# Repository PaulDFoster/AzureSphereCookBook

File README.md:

# AzureSphereCookBook
A collection of Azure Sphere code projects

1. Programmatic Reset: Programmatically trigger a Azure Sphere RDB reset using GPIO
2. Azure Blob Storage blob download using libcurl
3. Simple SPI communication. This project was built to demonstrate SPI comms to an ESP8266
4. SPI Flash Memory. Simple utilisation of an SPI flash memory to extend storage
5. Cifar10 CMSIS-NN example for Azure Sphere Cortex-M4F core
6. Eagle library for AI-Link WF-M620 modules
7. CI/CD testing board for WF-620 modules coupled with Adafruit Feather devices/accessories
8. C++ Toolchain files for RTCore C++ compilation
9. Tensorflow Lite for Microcontroller micro speech demo for Azure Sphere RTApp.
10. Generated micro speech Tensorflow lite for microcontroller library for use with 9)

ML on MCU briefing paper: Technology briefing The future of deep learning is 8-bit

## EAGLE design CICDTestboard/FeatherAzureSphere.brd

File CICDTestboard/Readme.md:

# CICD Test Board.
2nd July 2019

This folder contains two Eagle PCB projects:

1. Feather Azure Sphere
1. Feather Azure Sphere Long Tail

Number 1: Feather Azure Sphere

Is intended to provide a flexible CI/CD host for the WF-MT620 module, connecting it with any Adafruit Feather compatible MCU board or Feather Wing board. The idea is that the Feather board can be used to emulate hardware devices for the purposes of testing Azure Sphere code, or be the actual devices on a Feather Wing.

Connections are stated on the PCB, and include ADC, SPI and I2C as well as control connections for CHPD (Feather MCU enable) and Feather Reset.

Jumper JP1 can connected the Feather 3v to the MT620 3v power line. This can be used to power both modules from a single power source. CARE MUST be taken not to connect both modules to independent power sources when this jumper is connected(set). No power protection is implemented to allow the unit to be powered from either module.

THIS IS A TEST DESIGN. TESTING IS CURRENTLY OUTSTANDING.
Test results will be documented here.

Number 2 Feather Azure Sphere Long Tail

Is the starting point of a design to have an Azure Sphere board more closely sized to the Adafruit Feather boards.

It is incomplete and untested at this point in time.

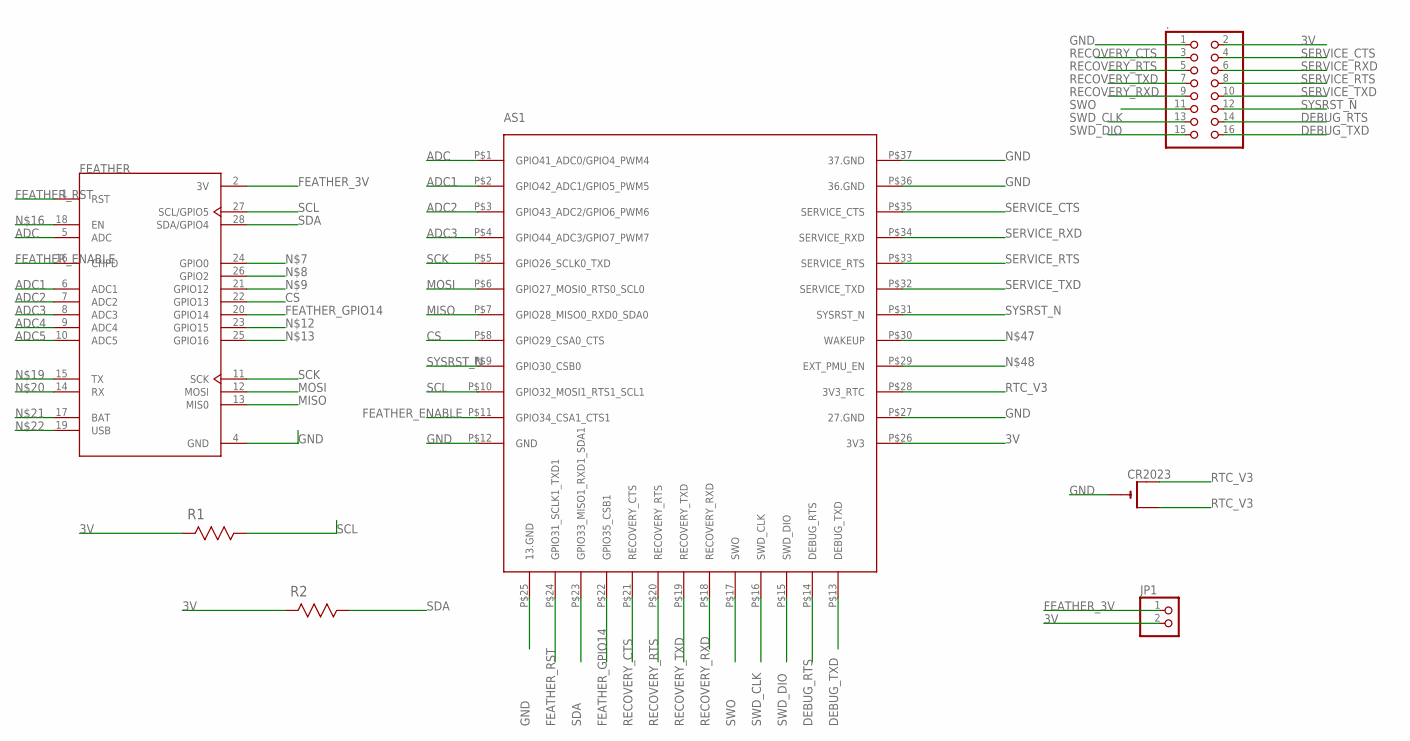
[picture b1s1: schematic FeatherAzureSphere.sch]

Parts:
.: PINHD-2X8; 2X08
AS1: WF-M620-RSC1
CR2023: CR2032SMT; CR2032-SMD
FEATHER: 2821; XCVR_2821
JP1: PINHD-1X2; 1X02
R1, R2: ERJ-8RQF1R5V; RESC3216X71N

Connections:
3V: ..2, AS1.P$26 (3V3), JP1.2, R1.2 (R2), R2.2 (R2)
ADC: AS1.P$1 (GPIO41_ADC0/GPIO4_PWM4), FEATHER.5 (ADC)
ADC1: AS1.P$2 (GPIO42_ADC1/GPIO5_PWM5), FEATHER.6 (ADC1)
ADC2: AS1.P$3 (GPIO43_ADC2/GPIO6_PWM6), FEATHER.7 (ADC2)
ADC3: AS1.P$4 (GPIO44_ADC3/GPIO7_PWM7), FEATHER.8 (ADC3)
ADC4: FEATHER.9 (ADC4)
ADC5: FEATHER.10 (ADC5)
CS: AS1.P$8 (GPIO29_CSA0_CTS), FEATHER.22 (GPIO13)
DEBUG_RTS: ..14, AS1.P$14 (DEBUG_RTS)
DEBUG_TXD: ..16, AS1.P$13 (DEBUG_TXD)
FEATHER_3V: FEATHER.2 (3V), JP1.1
FEATHER_ENABLE: AS1.P$11 (GPIO34_CSA1_CTS1), FEATHER.16 (CHPD)
FEATHER_GPIO14: AS1.P$22 (GPIO35_CSB1), FEATHER.20 (GPIO14)
FEATHER_RST: AS1.P$24 (GPIO31_SCLK1_TXD1), FEATHER.1 (RST)
GND: ..1, AS1.P$12 (GND), AS1.P$25 (13.GND), AS1.P$27 (27.GND), AS1.P$36 (36.GND), AS1.P$37 (37.GND), CR2023.-, FEATHER.4 (GND)
MISO: AS1.P$7 (GPIO28_MISO0_RXD0_SDA0), FEATHER.13 (MIS0)
MOSI: AS1.P$6 (GPIO27_MOSI0_RTS0_SCL0), FEATHER.12 (MOSI)
RECOVERY_CTS: ..3, AS1.P$21 (RECOVERY_CTS)
RECOVERY_RTS: ..5, AS1.P$20 (RECOVERY_RTS)
RECOVERY_RXD: ..9, AS1.P$18 (RECOVERY_RXD)
RECOVERY_TXD: ..7, AS1.P$19 (RECOVERY_TXD)
RTC_V3: AS1.P$28 (3V3_RTC), CR2023.+$1 (+), CR2023.+$2 (+1)
SCK: AS1.P$5 (GPIO26_SCLK0_TXD), FEATHER.11 (SCK)
SCL: AS1.P$10 (GPIO32_MOSI1_RTS1_SCL1), FEATHER.27 (SCL/GPIO5), R1.1 (R1)
SDA: AS1.P$23 (GPIO33_MISO1_RXD1_SDA1), FEATHER.28 (SDA/GPIO4), R2.1 (R1)
SERVICE_CTS: ..4, AS1.P$35 (SERVICE_CTS)
SERVICE_RTS: ..8, AS1.P$33 (SERVICE_RTS)
SERVICE_RXD: ..6, AS1.P$34 (SERVICE_RXD)
SERVICE_TXD: ..10, AS1.P$32 (SERVICE_TXD)
SWD_CLK: ..13, AS1.P$16 (SWD_CLK)
SWD_DIO: ..15, AS1.P$15 (SWD_DIO)
SWO: ..11, AS1.P$17 (SWO)
SYSRST_N: ..12, AS1.P$9 (GPIO30_CSB0), AS1.P$31 (SYSRST_N)

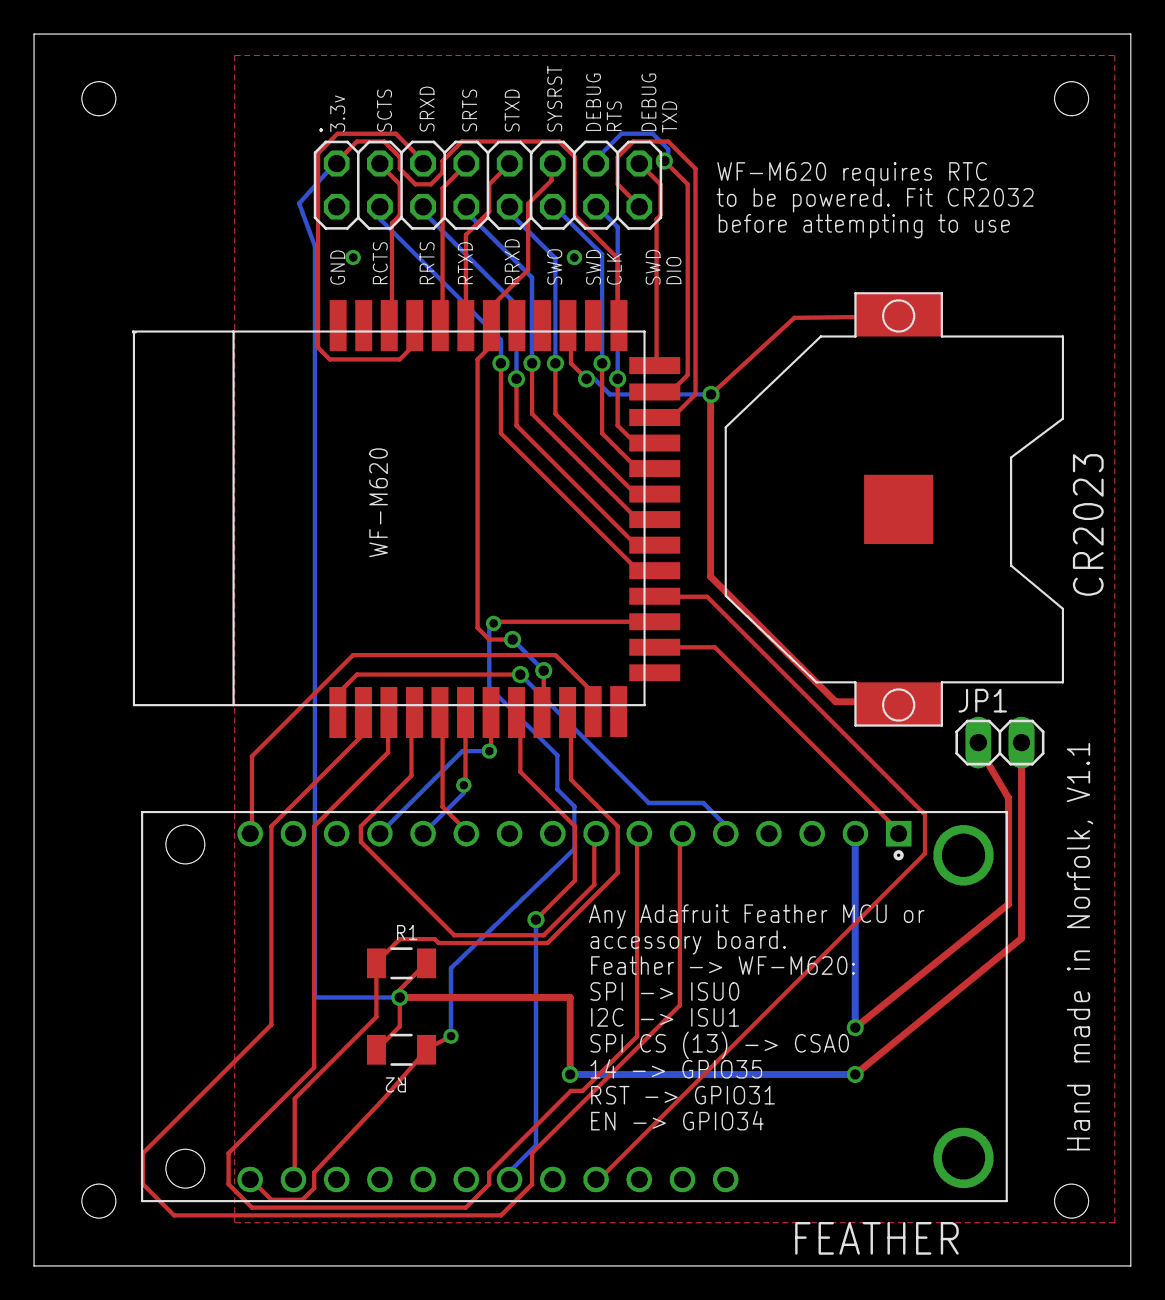
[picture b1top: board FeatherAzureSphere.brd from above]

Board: 2 copper layers, 64.4 x 72.4 mm, 7 parts (0 on the bottom side), 31 nets.

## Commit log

2019-05-03 Initial commit - Programmatic Reset
2019-05-03 Blob download example
2019-05-03 Simple SPI
2019-05-03 Correcting app_manifest typo
2019-05-22 SPI flash memory working
2019-05-29 Eagle CAD Library for AI-Link modules
2019-06-12 CMSIS NN Cifar10 example for Cortex-M4F core
2019-06-12 Added CIFAR project
    The CIFAR project implements the CMSIS NN library for an Azure Sphere Cortext-M4 core.
2019-06-12 Update Cifar10 example ReadMe files
2019-06-12 Removed unrequired original readme
2019-07-02 WF-M620-RSC1 corrections
    Discovered pin assignment was incorrect due to ordering. Now corrected.
2019-07-02 CICD Board design
    Board design is currently untested awaiting board delivery.
2019-07-02 Added CICD board pcb image
2019-07-05 Added Eagle projects
2019-07-05 Spelling corrections
2019-07-10 Correction of RSC1 module footprint
    The RSC1 footprint was flawed and has been corrected. Impacted board updated.
2019-07-25 Added ML on MCU short breifing paper
2019-07-25 updated briefing
2019-08-15 C++ RTCore compilation
    Added the C++ toolchain and the app linker script that enables C++ to be compiled to run on an Azure Sphere RTCore.
2019-08-21 Added TFLite MicroSpeech
    Added TFLite MicroSpeech demonstration
2019-08-21 Micro speech library
    The Tensorflow for microcontroller micro speech project as a static library for Azure Sphere. The library is used by the TFLiteHost_RTApp_MT3620_BareMetal app
2019-08-21 remove junk
